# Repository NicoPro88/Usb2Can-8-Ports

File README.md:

# Usb2Can-8-Ports

Carte électronique offrant **8 ports CAN** (jusqu'à **500 kbit/s** chacun) reliés à un PC par **un seul port USB**.

## Objectif

- 8 bus CAN indépendants, isolés ou non (à décider), débit nominal 500 kbit/s (CAN 2.0B, CAN FD envisageable).
- Connexion hôte en USB (USB 2.0 Full Speed ou High Speed, à décider selon la charge).
- Compatibilité visée côté PC : SocketCAN (Linux) et, si possible, un protocole ouvert type gs_usb / candleLight.
- Conception matérielle sous KiCad, firmware embarqué et documentation versionnés dans ce dépôt.

## Organisation du dépôt

| Dossier | Contenu |
|---|---|
| `hardware/` | Projet KiCad (schéma, PCB, bibliothèques, fichiers de fabrication) |
| `firmware/` | Code embarqué du microcontrôleur |
| `docs/` | Cahier des charges, choix d'architecture, notes de conception |

## État

- Architecture décidée : voir [`docs/decisions.md`](docs/decisions.md) (D1 à D6).
- Schéma v0.2 : [`docs/schema-bloc.md`](docs/schema-bloc.md) et [`hardware/`](hardware/).
- Placement des composants des deux cartes (non routé) : [`docs/placement.md`](docs/placement.md).

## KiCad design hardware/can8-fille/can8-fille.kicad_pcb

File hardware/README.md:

# Matériel

Deux cartes empilées (décision D3) :

| Dossier | Carte | Contenu |
|---|---|---|
| `can8-mere/` | Carte mère, 4 couches | STM32H723ZGT6, PHY USB3320 (USB HS), alimentation 9-36 V, ports CAN 1 à 4 |
| `can8-fille/` | Carte fille, 4 couches | ports CAN 5 à 8, reliée par un connecteur 2 × 20 |
| `bibliotheque/` | | symboles absents de la bibliothèque KiCad (USB3320C, ISO1042, UCC12050, MCP2518FD SOIC) |
| `outils/` | | générateur des schémas, vérification de la netlist, placement, routage, sorties de fabrication ; `retouches_mere_v03/` : trace des retouches de la carte mère |
| `fab/v0.3/` | | sorties de la v0.3 : Gerber et perçages, nomenclature, placement CMS, PDF, rendus, pour les deux cartes (le modèle STEP est régénéré par `outils/exporter.sh`, hors git) |

Chaque projet contient le schéma KiCad (`.kicad_pro`, `.kicad_sch`), un export PDF (`*-schema.pdf`), la nomenclature (`*-nomenclature.csv`), le circuit imprimé routé (`.kicad_pcb`, règles complémentaires dans `.kicad_dru`) et la vue PDF du placement v0.2 (`*-placement.pdf`). Les projets s'ouvrent dans **KiCad 9**.
Le schéma-bloc, l'affectation des broches et les points à vérifier sont dans [`docs/schema-bloc.md`](../docs/schema-bloc.md).

## État : v0.3, routage

4 couches, plans de masse et d'alimentation internes pleins. DRC de KiCad 9 sans erreur avec les règles du projet, parité schéma / circuit comprise, sur les deux cartes.

- **Carte fille** : routée à 100 %, sorties de fabrication complètes dans `fab/v0.3/can8-fille/`.
- **Carte mère** : routée à 100 % après une deuxième passe (placement retouché autour du PHY USB, bus ULPI re-tiré, ~INT1 à ~INT3 déplacées sur PG0, PG1, PA11), sorties de fabrication complètes dans `fab/v0.3/can8-mere/`. Avant de commander : relecture dans KiCad et vias dans les pastilles à faire boucher ou à décaler (`docs/routage.md` § 7).

Méthode, résultats, retouches de la carte mère, ce qui est vérifié et ce qui ne l'est pas : [`docs/routage.md`](../docs/routage.md).

```sh
# routage (KiCad 9 + Freerouting 2.5), voir docs/routage.md § 8
python3 hardware/outils/router.py preparer|importer|completer|finir|rapport can8-mere
# sorties de fabrication et rendus dans hardware/fab/v0.3/
sh hardware/outils/exporter.sh v0.3
```

## v0.2 : schémas et placement

Les schémas ont été générés par `outils/generer_schemas.py`, qui décrit chaque carte sous forme de netlist (composant, broche, net) et la dessine en KiCad 7 (lisible par KiCad 8 et 9). `outils/verifier_netlist.py` relit la netlist exportée par `kicad-cli` et la compare à la description : 0 écart sur les deux cartes.

Le dessin est fonctionnel mais brut (étiquettes de nets sur chaque broche). Une fois le schéma validé, on le retouche directement dans KiCad ; le générateur ne doit alors plus être relancé.

Le placement des deux cartes est généré par `outils/placer.py` : gros composants à des positions fixées, passifs placés automatiquement au plus près de leurs broches, contrôles des chevauchements, de la barrière d'isolement, de l'empilage des deux cartes et DRC de KiCad. Détails, images et points à valider : [`docs/placement.md`](../docs/placement.md).

```sh
# régénérer et vérifier (nécessite KiCad 7 : kicad-cli, kicad-symbols, kicad-footprints, module Python pcbnew)
python3 hardware/outils/verifier_netlist.py   # schémas + netlist
python3 hardware/outils/placer.py             # schémas + circuits imprimés placés
```

Les sorties de fabrication (Gerber, BOM, pick & place) sont dans `hardware/fab/<version>/`.

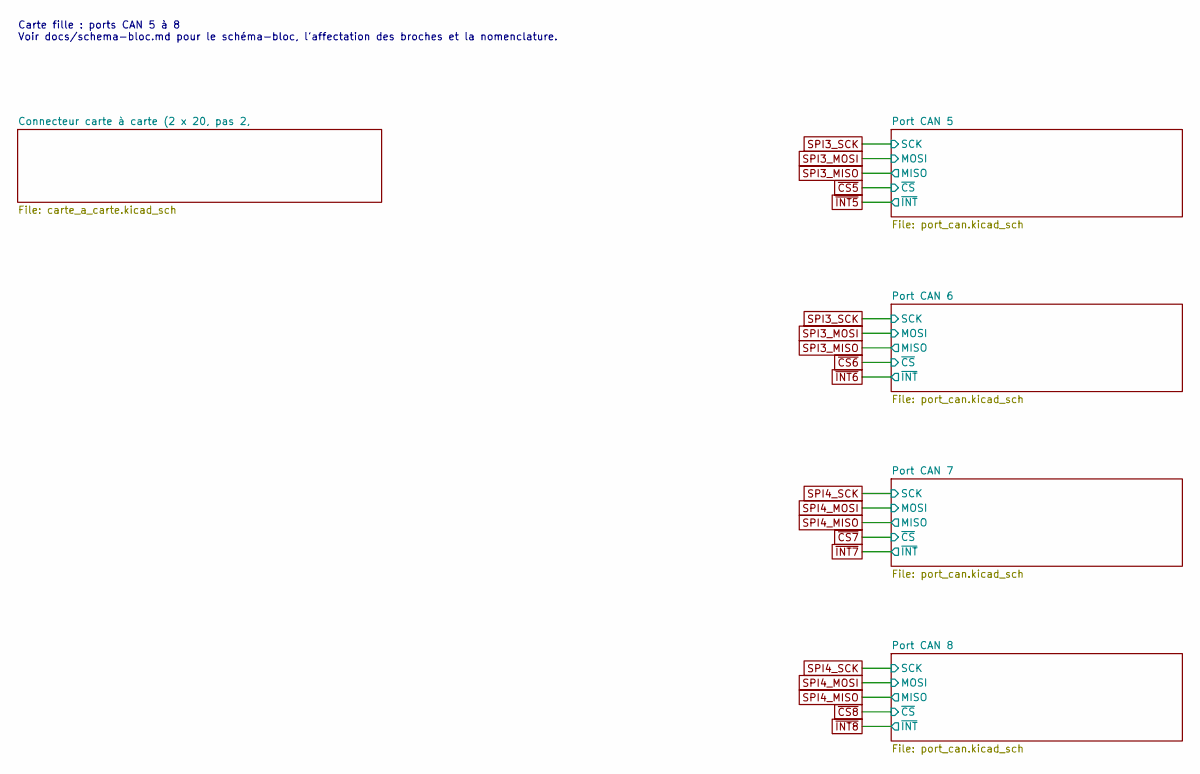
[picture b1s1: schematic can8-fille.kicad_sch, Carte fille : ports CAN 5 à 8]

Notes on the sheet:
Carte fille : ports CAN 5 à 8 Voir docs/schema-bloc.md pour le schéma-bloc, l'affectation des broches et la nomenclature.

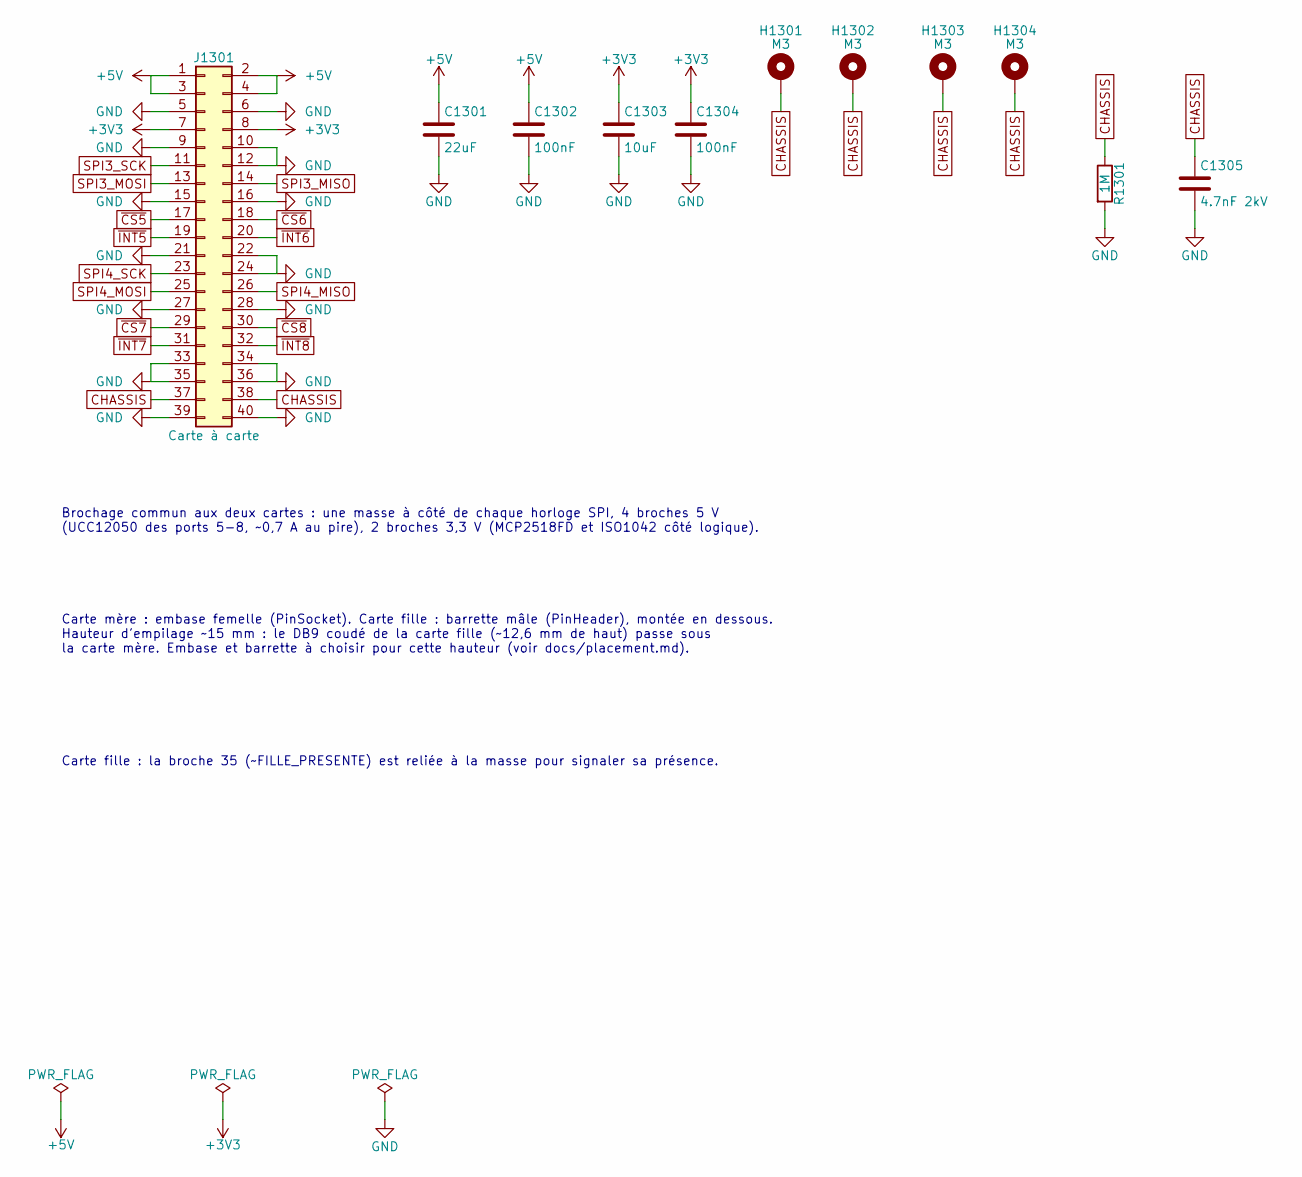
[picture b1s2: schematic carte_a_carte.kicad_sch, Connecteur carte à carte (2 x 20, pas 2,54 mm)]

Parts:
C1301: 22uF; C_1210_3225Metric
C1302, C1304: 100nF; C_0603_1608Metric
C1303: 10uF; C_0805_2012Metric
C1305: 4.7nF 2kV; C_1206_3216Metric
H1301, H1302, H1303, H1304: M3; MountingHole_3.2mm_M3_Pad_Via
J1301: Carte à carte; PinHeader_2x20_P2.54mm_Vertical
R1301: 1M; R_0603_1608Metric

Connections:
+3V3: C1303.1, C1304.1, J1301.7, J1301.8; also elsewhere on the board
+5V: C1301.1, C1302.1, J1301.1, J1301.2, J1301.3, J1301.4; also elsewhere on the board
CHASSIS: C1305.1, H1301.1, H1302.1, H1303.1, H1304.1, J1301.37, J1301.38, R1301.1; also elsewhere on the board
GND: C1301.2, C1302.2, C1303.2, C1304.2, C1305.2, J1301.5, J1301.6, J1301.9, J1301.10, J1301.12, J1301.15, J1301.16, J1301.21, J1301.22, J1301.24, J1301.27, J1301.28, J1301.33, J1301.34, J1301.35, J1301.36, J1301.39, J1301.40, R1301.2; also elsewhere on the board
SPI3_MISO: J1301.14; also elsewhere on the board
SPI3_MOSI: J1301.13; also elsewhere on the board
SPI3_SCK: J1301.11; also elsewhere on the board
SPI4_MISO: J1301.26; also elsewhere on the board
SPI4_MOSI: J1301.25; also elsewhere on the board
SPI4_SCK: J1301.23; also elsewhere on the board
~CS5: J1301.17; also elsewhere on the board
~CS6: J1301.18; also elsewhere on the board
~CS7: J1301.29; also elsewhere on the board
~CS8: J1301.30; also elsewhere on the board
~INT5: J1301.19; also elsewhere on the board
~INT6: J1301.20; also elsewhere on the board
~INT7: J1301.31; also elsewhere on the board
~INT8: J1301.32; also elsewhere on the board

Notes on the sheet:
Brochage commun aux deux cartes : une masse à côté de chaque horloge SPI, 4 broches 5 V (UCC12050 des ports 5-8, ~0,7 A au pire), 2 broches 3,3 V (MCP2518FD et ISO1042 côté logique).
Carte mère : embase femelle (PinSocket). Carte fille : barrette mâle (PinHeader), montée en dessous. Hauteur d'empilage ~15 mm : le DB9 coudé de la carte fille (~12,6 mm de haut) passe sous la carte mère. Embase et barrette à choisir pour cette hauteur (voir docs/placement.md).
Carte fille : la broche 35 (~FILLE_PRESENTE) est reliée à la masse pour signaler sa présence.

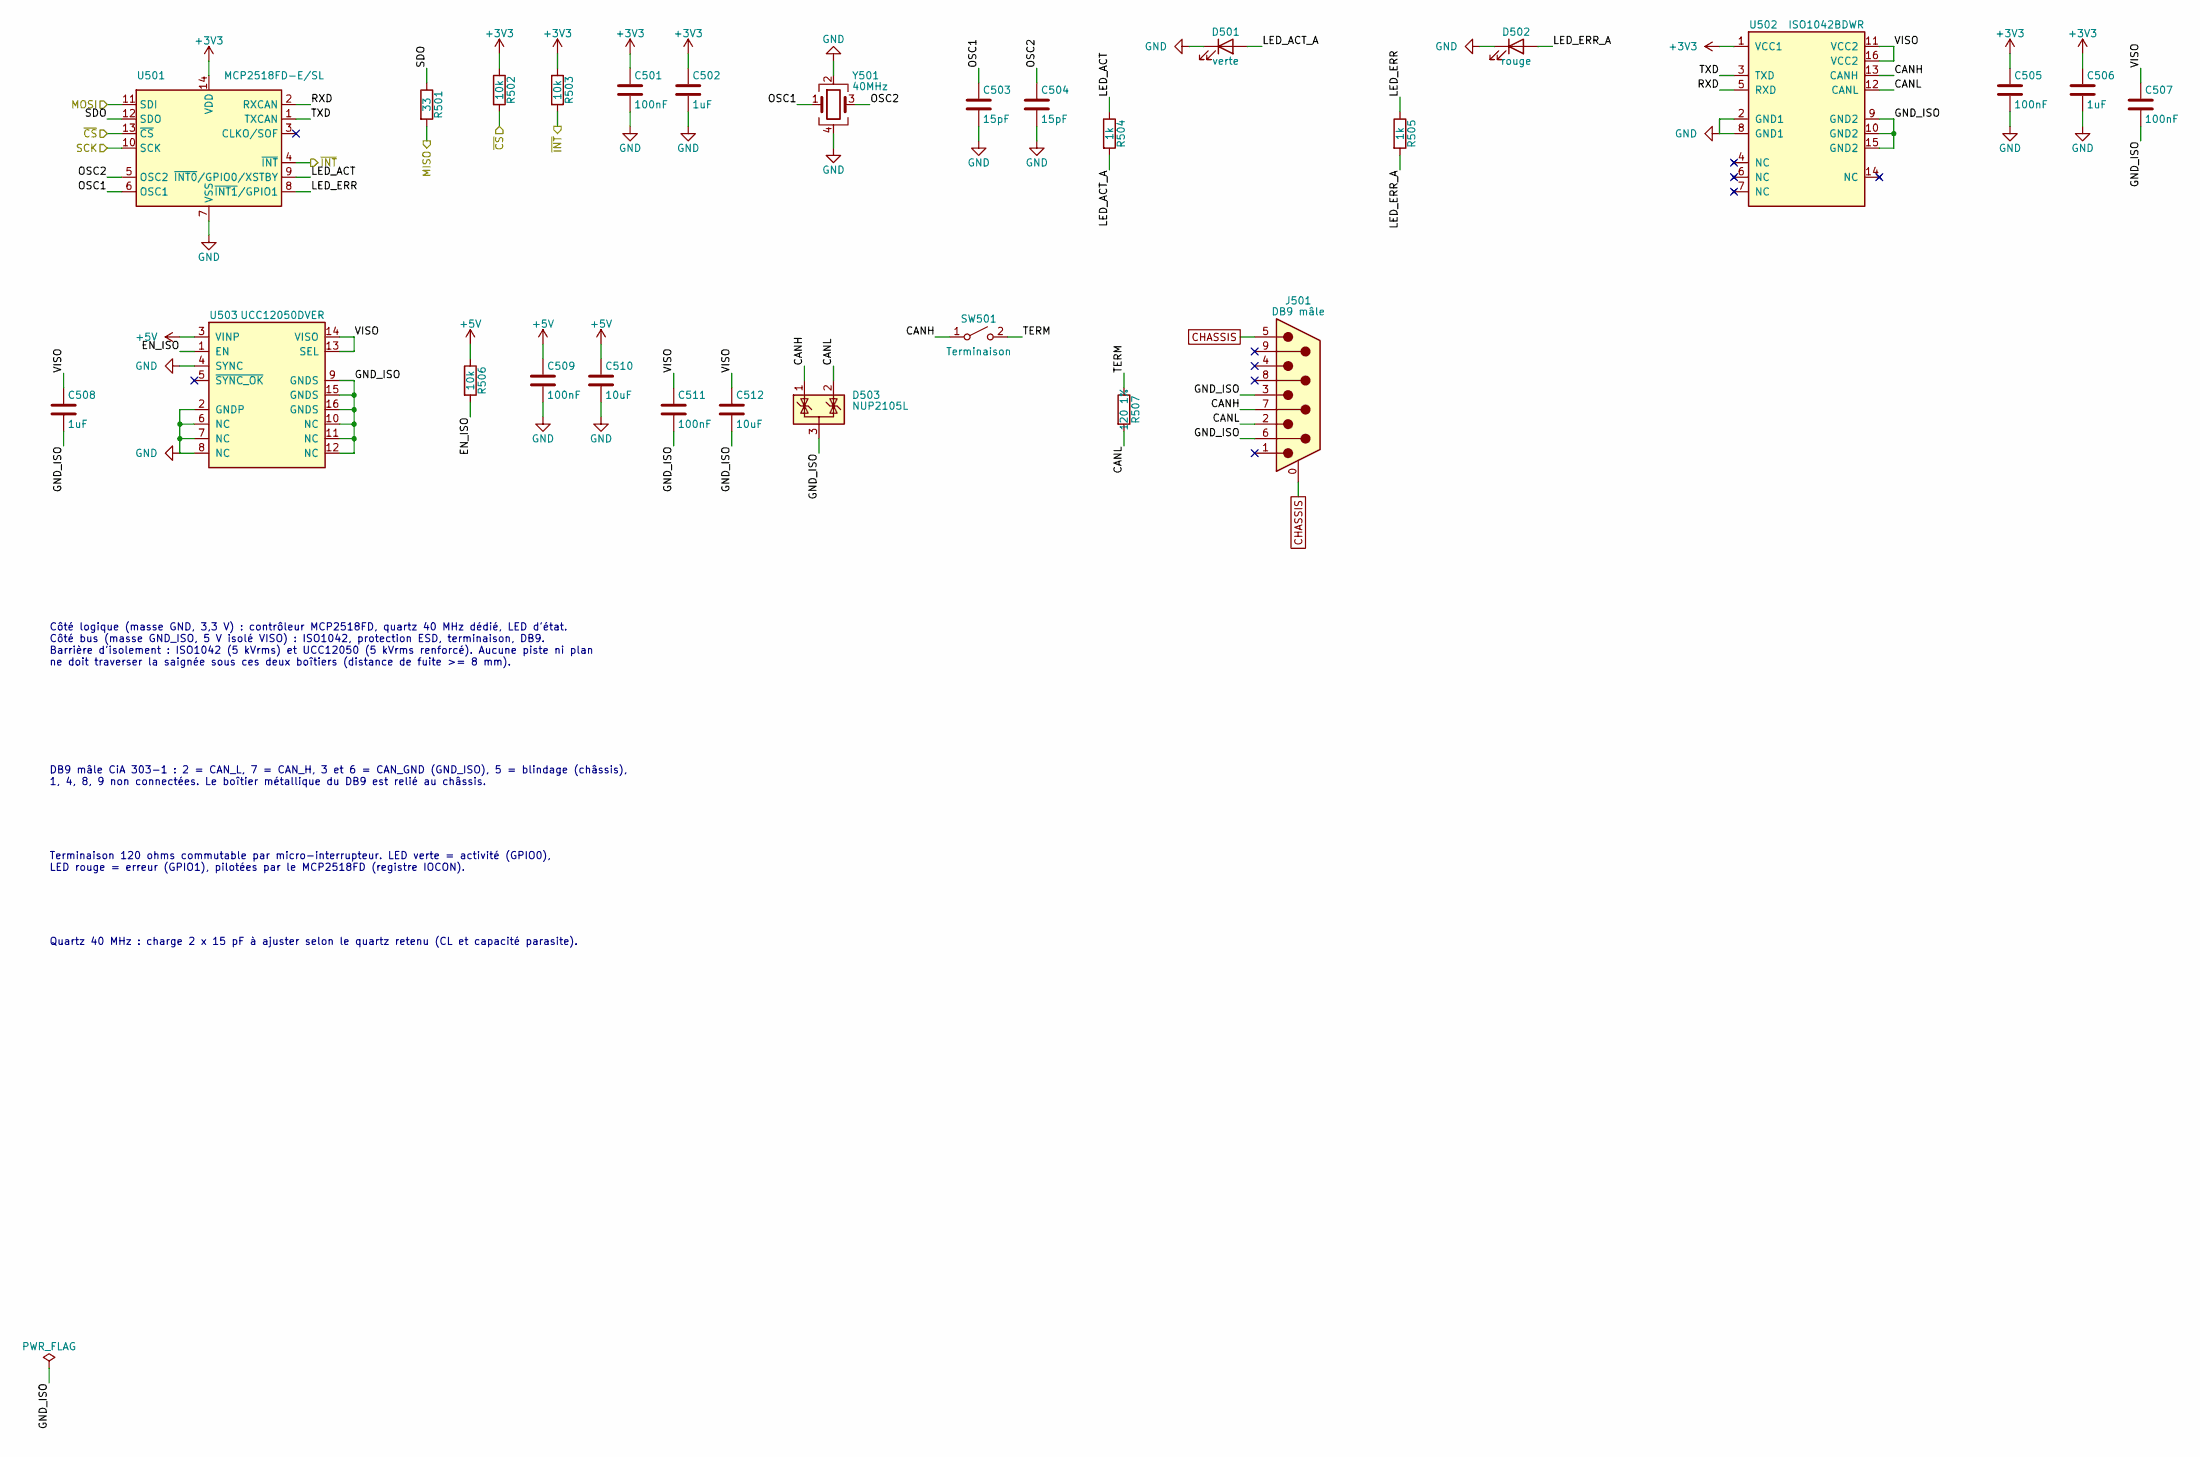
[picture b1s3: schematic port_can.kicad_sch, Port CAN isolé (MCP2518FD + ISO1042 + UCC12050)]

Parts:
C501, C505, C507, C509, C511: 100nF; C_0603_1608Metric
C502, C506, C508: 1uF; C_0805_2012Metric
C503, C504: 15pF; C_0603_1608Metric
C510, C512: 10uF; C_0805_2012Metric
D501: verte; LED_0603_1608Metric
D502: rouge; LED_0603_1608Metric
D503: NUP2105L; SOT-23
J501: DB9 mâle; DSUB-9_Pins_Horizontal_P2.77x2.84mm_EdgePinOffset9.90mm_Hou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
R501: 33; R_0603_1608Metric
R502, R503, R506: 10k; R_0603_1608Metric
R504, R505: 1k; R_0603_1608Metric
R507: 120 1%; R_1206_3216Metric
SW501: Terminaison; SW_DIP_SPSTx01_Slide_6.7x4.1mm_W8.61mm_P2.54mm_LowProfile
U501: MCP2518FD-E/SL; SOIC-14_3.9x8.7mm_P1.27mm
U502: ISO1042BDWR; SOIC-16W_7.5x10.3mm_P1.27mm
U503: UCC12050DVER; SOIC-16W_7.5x10.3mm_P1.27mm
Y501: 40MHz; Crystal_SMD_3225-4Pin_3.2x2.5mm

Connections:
+3V3: C501.1, C502.1, C505.1, C506.1, R502.1, R503.1, U501.14 (VDD), U502.1 (VCC1); also elsewhere on the board
+5V: C509.1, C510.1, R506.1, U503.3 (VINP); also elsewhere on the board
/Port CAN 5/CANH: D503.1 (K), J501.7, SW501.1 (A), U502.13 (CANH)
/Port CAN 5/CANL: D503.2 (K), J501.2, R507.2, U502.12 (CANL)
/Port CAN 5/EN_ISO: R506.2, U503.1 (EN)
/Port CAN 5/GND_ISO: C507.2, C508.2, C511.2, C512.2, D503.3 (A), J501.3, J501.6, U502.9 (GND2), U502.10 (GND2), U502.15 (GND2), U503.9 (GNDS), U503.10 (NC), U503.11 (NC), U503.12 (NC), U503.15 (GNDS), U503.16 (GNDS)
/Port CAN 5/LED_ACT: R504.1, U501.9 (~INT0/GPIO0/XSTBY)
/Port CAN 5/LED_ACT_A: D501.2 (A), R504.2
/Port CAN 5/LED_ERR: R505.1, U501.8 (~INT1/GPIO1)
/Port CAN 5/LED_ERR_A: D502.2 (A), R505.2
/Port CAN 5/OSC1: C503.1, U501.6 (OSC1), Y501.1
/Port CAN 5/OSC2: C504.1, U501.5 (OSC2), Y501.3
/Port CAN 5/RXD: U501.2 (RXCAN), U502.5 (RXD)
/Port CAN 5/SDO: R501.1, U501.12 (SDO)
/Port CAN 5/TERM: R507.1, SW501.2 (B)
/Port CAN 5/TXD: U501.1 (TXCAN), U502.3 (TXD)
/Port CAN 5/VISO: C507.1, C508.1, C511.1, C512.1, U502.11 (VCC2), U502.16 (VCC2), U503.13 (SEL), U503.14 (VISO)
CHASSIS: J501.0 (PAD), J501.5; also elsewhere on the board
GND: C501.2, C502.2, C503.2, C504.2, C505.2, C506.2, C509.2, C510.2, D501.1 (K), D502.1 (K), U501.7 (VSS), U502.2 (GND1), U502.8 (GND1), U503.2 (GNDP), U503.4 (SYNC), U503.6 (NC), U503.7 (NC), U503.8 (NC), Y501.2, Y501.4; also elsewhere on the board
SPI3_MISO: R501.2; also elsewhere on the board
SPI3_MOSI: U501.11 (SDI); also elsewhere on the board
SPI3_SCK: U501.10 (SCK); also elsewhere on the board
~CS5: R502.2, U501.13 (~CS); also elsewhere on the board
~INT5: R503.2, U501.4 (~INT); also elsewhere on the board

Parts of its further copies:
C601, C605, C607, C609, C611, C701, C705, C707, C709, C711, C801, C805, C807, C809, C811: 100nF; C_0603_1608Metric
C602, C606, C608, C702, C706, C708, C802, C806, C808: 1uF; C_0805_2012Metric
C603, C604, C703, C704, C803, C804: 15pF; C_0603_1608Metric
C610, C612, C710, C712, C810, C812: 10uF; C_0805_2012Metric
D601, D701, D801: verte; LED_0603_1608Metric
D602, D702, D802: rouge; LED_0603_1608Metric
D603, D703, D803: NUP2105L; SOT-23
J601, J701, J801: DB9 mâle; DSUB-9_Pins_Horizontal_P2.77x2.84mm_EdgePinOffset9.90mm_Hou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
R601, R701, R801: 33; R_0603_1608Metric
R602, R603, R606, R702, R703, R706, R802, R803, R806: 10k; R_0603_1608Metric
R604, R605, R704, R705, R804, R805: 1k; R_0603_1608Metric
R607, R707, R807: 120 1%; R_1206_3216Metric
SW601, SW701, SW801: Terminaison; SW_DIP_SPSTx01_Slide_6.7x4.1mm_W8.61mm_P2.54mm_LowProfile
U601, U701, U801: MCP2518FD-E/SL; SOIC-14_3.9x8.7mm_P1.27mm
U602, U702, U802: ISO1042BDWR; SOIC-16W_7.5x10.3mm_P1.27mm
U603, U703, U803: UCC12050DVER; SOIC-16W_7.5x10.3mm_P1.27mm
Y601, Y701, Y801: 40MHz; Crystal_SMD_3225-4Pin_3.2x2.5mm

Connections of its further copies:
+3V3: C601.1, C602.1, C605.1, C606.1, C701.1, C702.1, C705.1, C706.1, C801.1, C802.1, C805.1, C806.1, R602.1, R603.1, R702.1, R703.1, R802.1, R803.1, U601.14 (VDD), U602.1 (VCC1), U701.14 (VDD), U702.1 (VCC1), U801.14 (VDD), U802.1 (VCC1); also elsewhere on the board
+5V: C609.1, C610.1, C709.1, C710.1, C809.1, C810.1, R606.1, R706.1, R806.1, U603.3 (VINP), U703.3 (VINP), U803.3 (VINP); also elsewhere on the board
/Port CAN 6/CANH: D603.1 (K), J601.7, SW601.1 (A), U602.13 (CANH)
/Port CAN 6/CANL: D603.2 (K), J601.2, R607.2, U602.12 (CANL)
/Port CAN 6/EN_ISO: R606.2, U603.1 (EN)
/Port CAN 6/GND_ISO: C607.2, C608.2, C611.2, C612.2, D603.3 (A), J601.3, J601.6, U602.9 (GND2), U602.10 (GND2), U602.15 (GND2), U603.9 (GNDS), U603.10 (NC), U603.11 (NC), U603.12 (NC), U603.15 (GNDS), U603.16 (GNDS)
/Port CAN 6/LED_ACT: R604.1, U601.9 (~INT0/GPIO0/XSTBY)
/Port CAN 6/LED_ACT_A: D601.2 (A), R604.2
/Port CAN 6/LED_ERR: R605.1, U601.8 (~INT1/GPIO1)
/Port CAN 6/LED_ERR_A: D602.2 (A), R605.2
/Port CAN 6/OSC1: C603.1, U601.6 (OSC1), Y601.1
/Port CAN 6/OSC2: C604.1, U601.5 (OSC2), Y601.3
/Port CAN 6/RXD: U601.2 (RXCAN), U602.5 (RXD)
/Port CAN 6/SDO: R601.1, U601.12 (SDO)
/Port CAN 6/TERM: R607.1, SW601.2 (B)
/Port CAN 6/TXD: U601.1 (TXCAN), U602.3 (TXD)
/Port CAN 6/VISO: C607.1, C608.1, C611.1, C612.1, U602.11 (VCC2), U602.16 (VCC2), U603.13 (SEL), U603.14 (VISO)
/Port CAN 7/CANH: D703.1 (K), J701.7, SW701.1 (A), U702.13 (CANH)
/Port CAN 7/CANL: D703.2 (K), J701.2, R707.2, U702.12 (CANL)
/Port CAN 7/EN_ISO: R706.2, U703.1 (EN)
/Port CAN 7/GND_ISO: C707.2, C708.2, C711.2, C712.2, D703.3 (A), J701.3, J701.6, U702.9 (GND2), U702.10 (GND2), U702.15 (GND2), U703.9 (GNDS), U703.10 (NC), U703.11 (NC), U703.12 (NC), U703.15 (GNDS), U703.16 (GNDS)
/Port CAN 7/LED_ACT: R704.1, U701.9 (~INT0/GPIO0/XSTBY)
/Port CAN 7/LED_ACT_A: D701.2 (A), R704.2
/Port CAN 7/LED_ERR: R705.1, U701.8 (~INT1/GPIO1)
/Port CAN 7/LED_ERR_A: D702.2 (A), R705.2
/Port CAN 7/OSC1: C703.1, U701.6 (OSC1), Y701.1
/Port CAN 7/OSC2: C704.1, U701.5 (OSC2), Y701.3
/Port CAN 7/RXD: U701.2 (RXCAN), U702.5 (RXD)
/Port CAN 7/SDO: R701.1, U701.12 (SDO)
/Port CAN 7/TERM: R707.1, SW701.2 (B)
/Port CAN 7/TXD: U701.1 (TXCAN), U702.3 (TXD)
/Port CAN 7/VISO: C707.1, C708.1, C711.1, C712.1, U702.11 (VCC2), U702.16 (VCC2), U703.13 (SEL), U703.14 (VISO)
/Port CAN 8/CANH: D803.1 (K), J801.7, SW801.1 (A), U802.13 (CANH)
/Port CAN 8/CANL: D803.2 (K), J801.2, R807.2, U802.12 (CANL)
/Port CAN 8/EN_ISO: R806.2, U803.1 (EN)
/Port CAN 8/GND_ISO: C807.2, C808.2, C811.2, C812.2, D803.3 (A), J801.3, J801.6, U802.9 (GND2), U802.10 (GND2), U802.15 (GND2), U803.9 (GNDS), U803.10 (NC), U803.11 (NC), U803.12 (NC), U803.15 (GNDS), U803.16 (GNDS)
/Port CAN 8/LED_ACT: R804.1, U801.9 (~INT0/GPIO0/XSTBY)
/Port CAN 8/LED_ACT_A: D801.2 (A), R804.2
/Port CAN 8/LED_ERR: R805.1, U801.8 (~INT1/GPIO1)
/Port CAN 8/LED_ERR_A: D802.2 (A), R805.2
/Port CAN 8/OSC1: C803.1, U801.6 (OSC1), Y801.1
/Port CAN 8/OSC2: C804.1, U801.5 (OSC2), Y801.3
/Port CAN 8/RXD: U801.2 (RXCAN), U802.5 (RXD)
/Port CAN 8/SDO: R801.1, U801.12 (SDO)
/Port CAN 8/TERM: R807.1, SW801.2 (B)
/Port CAN 8/TXD: U801.1 (TXCAN), U802.3 (TXD)
/Port CAN 8/VISO: C807.1, C808.1, C811.1, C812.1, U802.11 (VCC2), U802.16 (VCC2), U803.13 (SEL), U803.14 (VISO)
CHASSIS: J601.0 (PAD), J601.5, J701.0 (PAD), J701.5, J801.0 (PAD), J801.5; also elsewhere on the board
GND: C601.2, C602.2, C603.2, C604.2, C605.2, C606.2, C609.2, C610.2, C701.2, C702.2, C703.2, C704.2, C705.2, C706.2, C709.2, C710.2, C801.2, C802.2, C803.2, C804.2, C805.2, C806.2, C809.2, C810.2, D601.1 (K), D602.1 (K), D701.1 (K), D702.1 (K), D801.1 (K), D802.1 (K), U601.7 (VSS), U602.2 (GND1), U602.8 (GND1), U603.2 (GNDP), U603.4 (SYNC), U603.6 (NC), U603.7 (NC), U603.8 (NC), U701.7 (VSS), U702.2 (GND1), U702.8 (GND1), U703.2 (GNDP), U703.4 (SYNC), U703.6 (NC), U703.7 (NC), U703.8 (NC), U801.7 (VSS), U802.2 (GND1), U802.8 (GND1), U803.2 (GNDP), U803.4 (SYNC), U803.6 (NC), U803.7 (NC), U803.8 (NC), Y601.2, Y601.4, Y701.2, Y701.4, Y801.2, Y801.4; also elsewhere on the board
SPI3_MISO: R601.2; also elsewhere on the board
SPI3_MOSI: U601.11 (SDI); also elsewhere on the board
SPI3_SCK: U601.10 (SCK); also elsewhere on the board
SPI4_MISO: R701.2, R801.2; also elsewhere on the board
SPI4_MOSI: U701.11 (SDI), U801.11 (SDI); also elsewhere on the board
SPI4_SCK: U701.10 (SCK), U801.10 (SCK); also elsewhere on the board
~CS6: R602.2, U601.13 (~CS); also elsewhere on the board
~CS7: R702.2, U701.13 (~CS); also elsewhere on the board
~CS8: R802.2, U801.13 (~CS); also elsewhere on the board
~INT6: R603.2, U601.4 (~INT); also elsewhere on the board
~INT7: R703.2, U701.4 (~INT); also elsewhere on the board
~INT8: R803.2, U801.4 (~INT); also elsewhere on the board

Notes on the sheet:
Côté logique (masse GND, 3,3 V) : contrôleur MCP2518FD, quartz 40 MHz dédié, LED d'état. Côté bus (masse GND_ISO, 5 V isolé VISO) : ISO1042, protection ESD, terminaison, DB9. Barrière d'isolement : ISO1042 (5 kVrms) et UCC12050 (5 kVrms renforcé). Aucune piste ni plan ne doit traverser la saignée s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
DB9 mâle CiA 303-1 : 2 = CAN_L, 7 = CAN_H, 3 et 6 = CAN_GND (GND_ISO), 5 = blindage (châssis), 1, 4, 8, 9 non connectées. Le boîtier métallique du DB9 est relié au châssis.
Terminaison 120 ohms commutable par micro-interrupteur. LED verte = activité (GPIO0), LED rouge = erreur (GPIO1), pilotées par le MCP2518FD (registre IOCON).
Quartz 40 MHz : charge 2 x 15 pF à ajuster selon le quartz retenu (CL et capacité parasite).

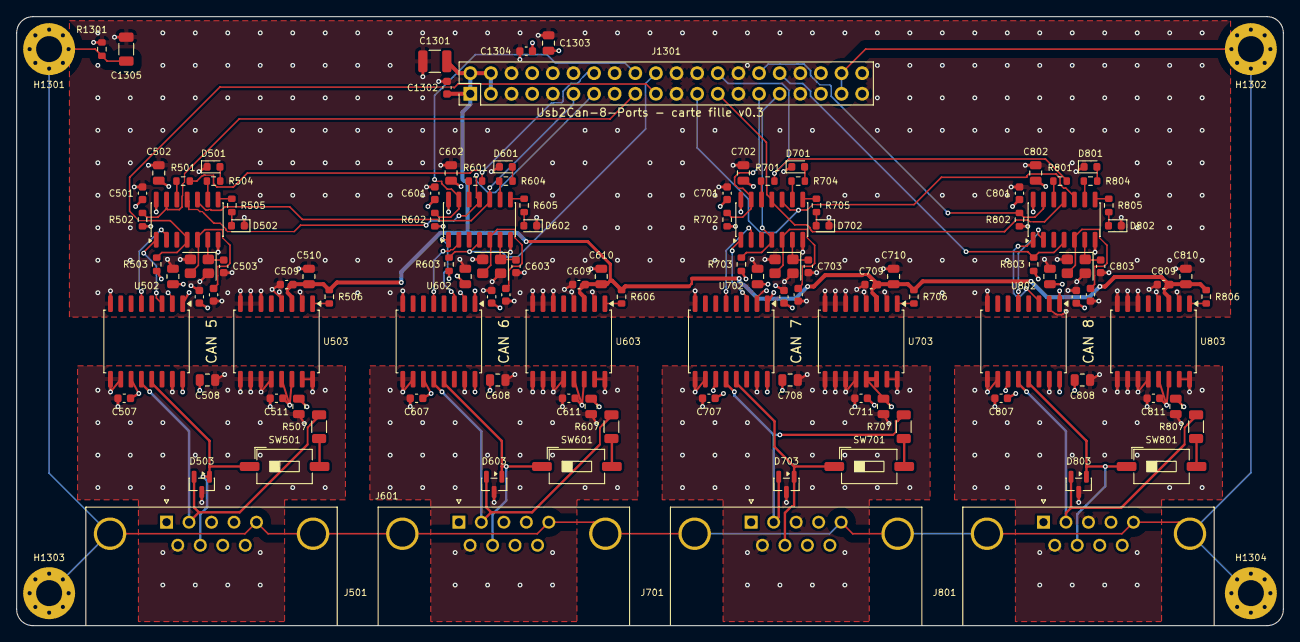
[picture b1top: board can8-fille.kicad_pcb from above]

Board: 4 copper layers, 156.0 x 75.0 mm, 123 parts (0 on the bottom side), 78 nets.

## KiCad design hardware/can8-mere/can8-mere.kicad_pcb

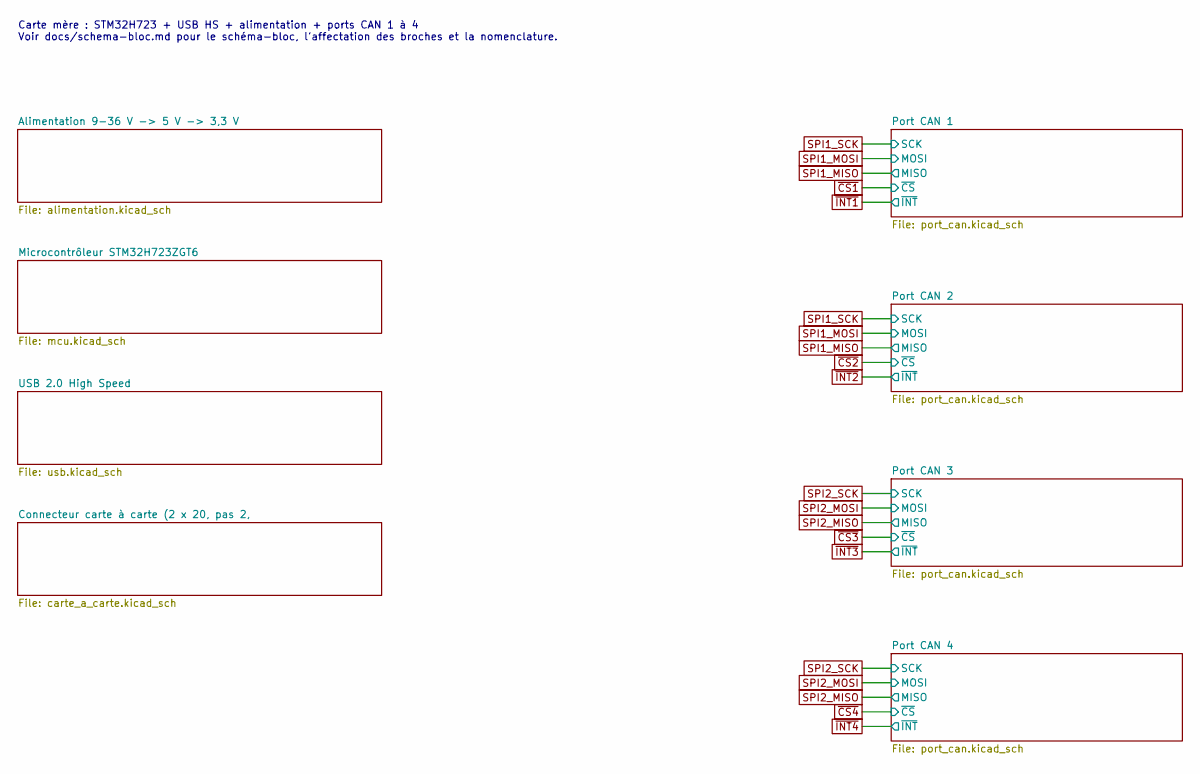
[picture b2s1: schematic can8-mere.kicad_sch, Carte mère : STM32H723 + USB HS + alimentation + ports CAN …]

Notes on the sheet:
Carte mère : STM32H723 + USB HS + alimentation + ports CAN 1 à 4 Voir docs/schema-bloc.md pour le schéma-bloc, l'affectation des broches et la nomenclature.

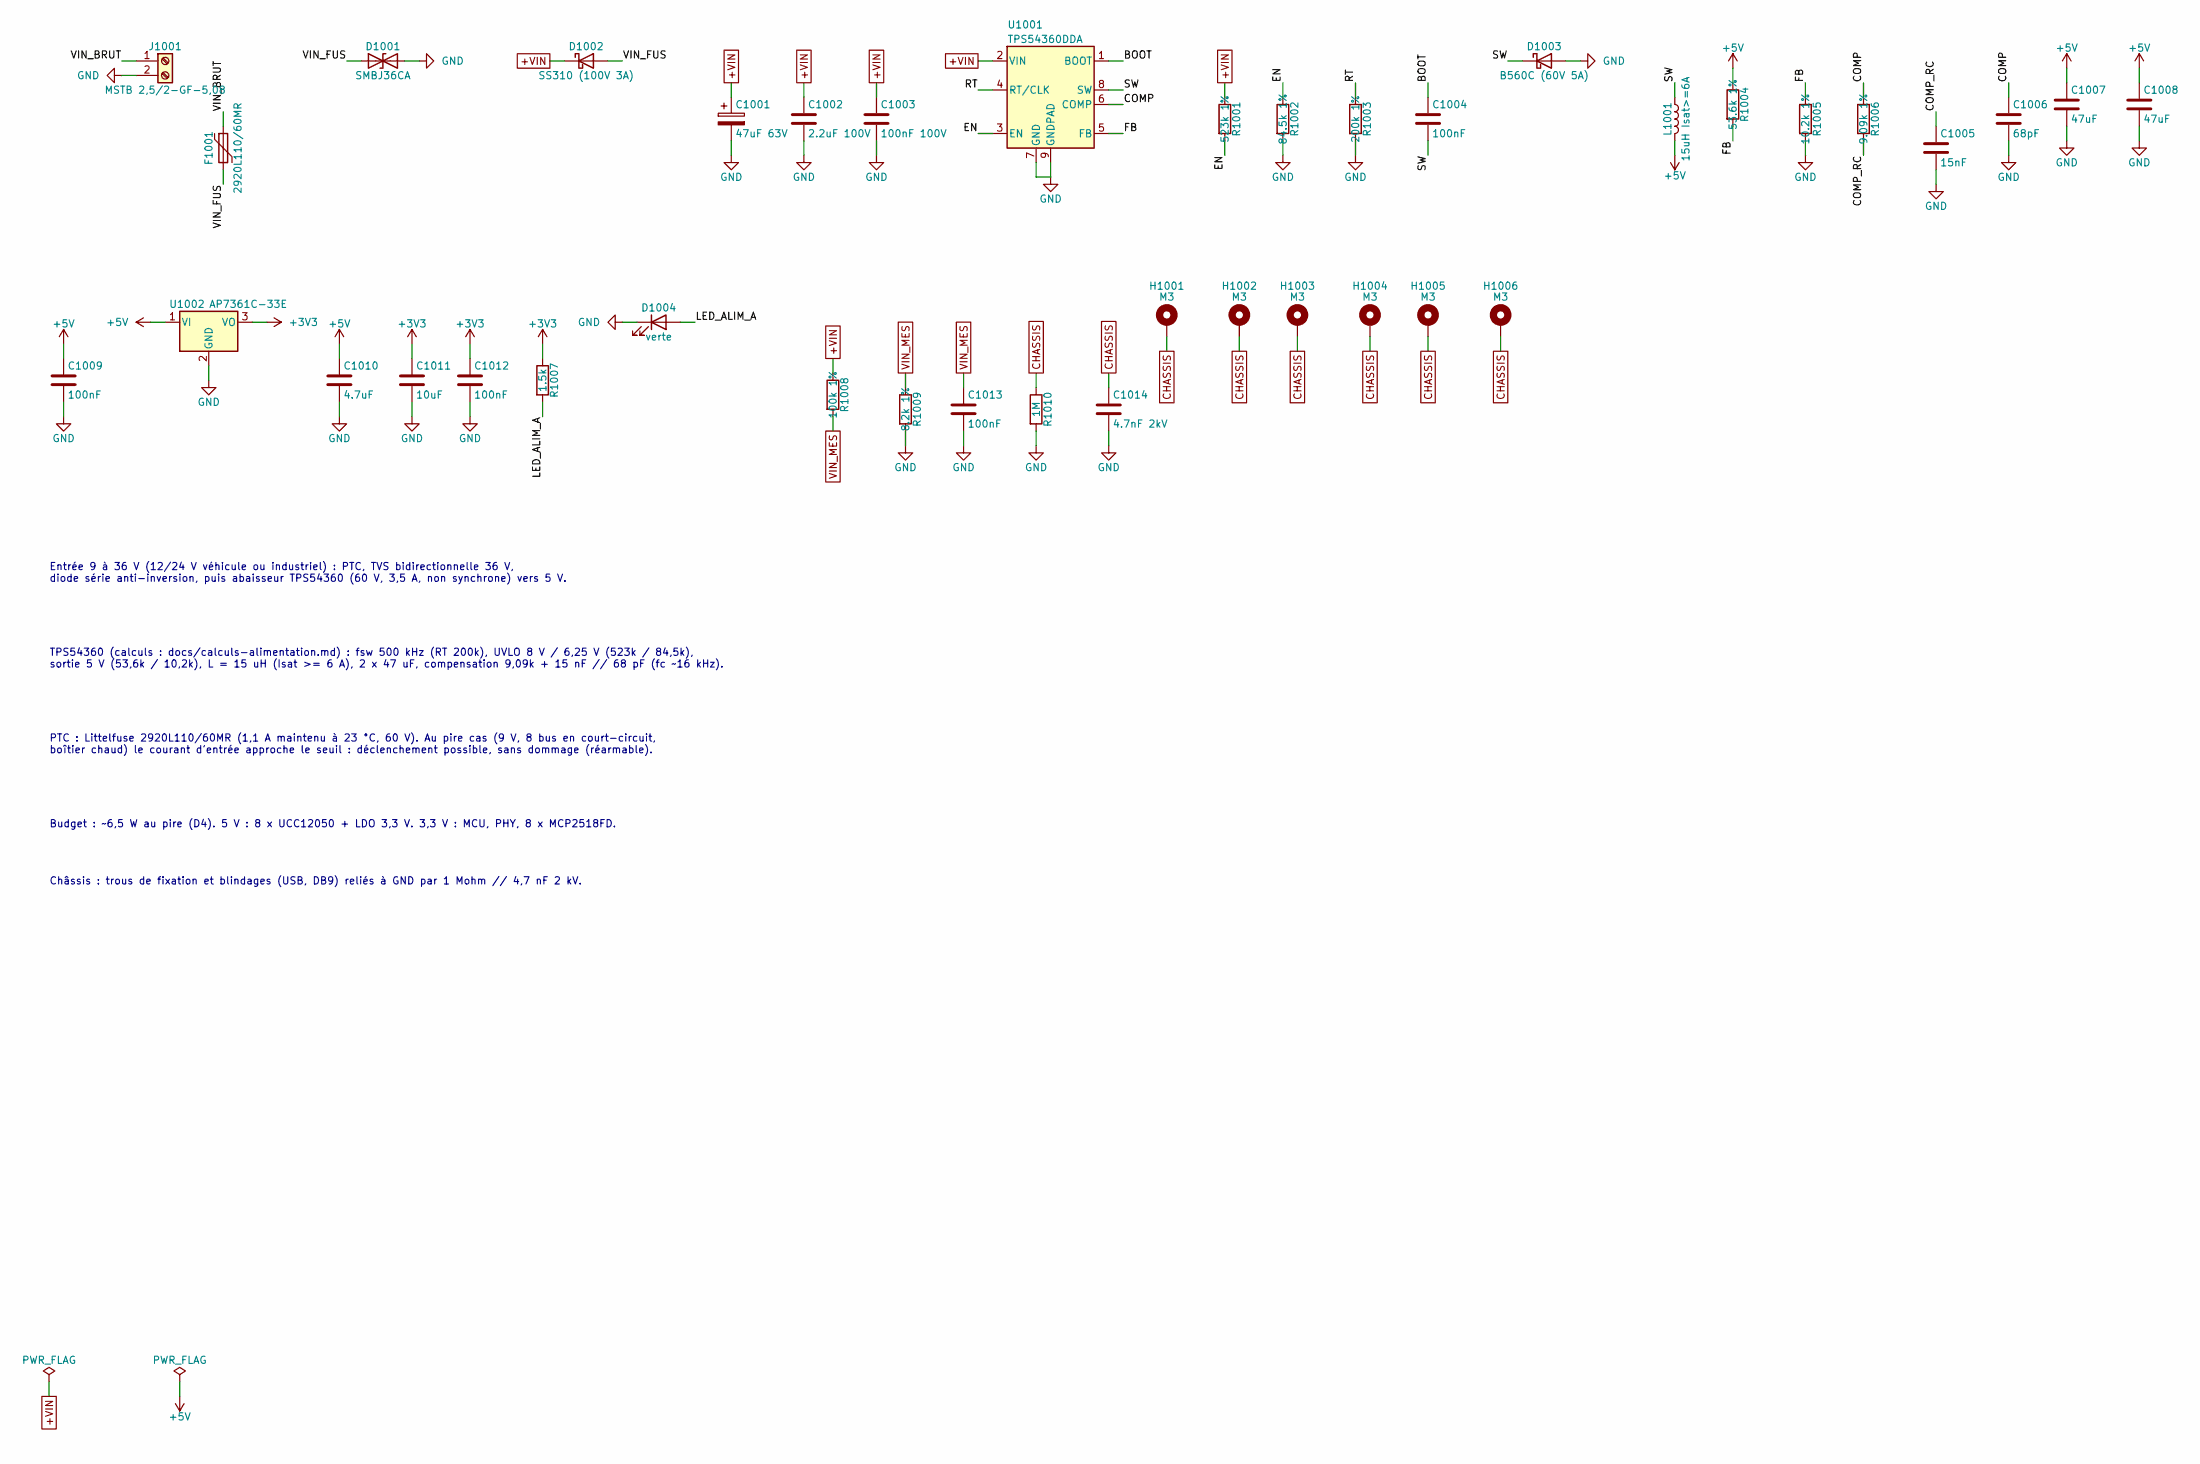
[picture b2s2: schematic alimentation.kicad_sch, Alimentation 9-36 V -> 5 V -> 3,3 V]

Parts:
C1001: 47uF 63V; CP_Elec_8x10
C1002: 2.2uF 100V; C_1210_3225Metric
C1003: 100nF 100V; C_0805_2012Metric
C1004, C1009, C1012, C1013: 100nF; C_0603_1608Metric
C1005: 15nF; C_0603_1608Metric
C1006: 68pF; C_0603_1608Metric
C1007, C1008: 47uF; C_1210_3225Metric
C1010: 4.7uF; C_0805_2012Metric
C1011: 10uF; C_0805_2012Metric
C1014: 4.7nF 2kV; C_1206_3216Metric
D1001: SMBJ36CA; D_SMB
D1002: SS310 (100V 3A); D_SMA
D1003: B560C (60V 5A); D_SMC
D1004: verte; LED_0603_1608Metric
F1001: 2920L110/60MR; Fuse_2920_7451Metric
H1001, H1002, H1003, H1004, H1005, H1006: M3; MountingHole_3.2mm_M3_Pad_Via
J1001: MSTB 2,5/2-GF-5,08; PhoenixContact_MSTB_2,5_2-GF-5,08_1x02_P5.08mm_Horizontal_T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
L1001: 15uH Isat>=6A; L_Bourns_SRP1038C_10.0x10.0mm
R1001: 523k 1%; R_0603_1608Metric
R1002: 84.5k 1%; R_0603_1608Metric
R1003: 200k 1%; R_0603_1608Metric
R1004: 53.6k 1%; R_0603_1608Metric
R1005: 10.2k 1%; R_0603_1608Metric
R1006: 9.09k 1%; R_0603_1608Metric
R1007: 1.5k; R_0603_1608Metric
R1008: 100k 1%; R_0603_1608Metric
R1009: 8.2k 1%; R_0603_1608Metric
R1010: 1M; R_0603_1608Metric
U1001: TPS54360DDA; TI_SO-PowerPAD-8_ThermalVias
U1002: AP7361C-33E; SOT-223-3_TabPin2

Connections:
+3V3: C1011.1, C1012.1, R1007.1, U1002.3 (VO); also elsewhere on the board
+5V: C1007.1, C1008.1, C1009.1, C1010.1, L1001.2, R1004.1, U1002.1 (VI); also elsewhere on the board
+VIN: C1001.1, C1002.1, C1003.1, D1002.1 (K), R1001.1, R1008.1, U1001.2 (VIN)
/Alimentation 9-36 V -> 5 V -> 3,3 V/BOOT: C1004.1, U1001.1 (BOOT)
/Alimentation 9-36 V -> 5 V -> 3,3 V/COMP: C1006.1, R1006.1, U1001.6 (COMP)
/Alimentation 9-36 V -> 5 V -> 3,3 V/COMP_RC: C1005.1, R1006.2
/Alimentation 9-36 V -> 5 V -> 3,3 V/EN: R1001.2, R1002.1, U1001.3 (EN)
/Alimentation 9-36 V -> 5 V -> 3,3 V/FB: R1004.2, R1005.1, U1001.5 (FB)
/Alimentation 9-36 V -> 5 V -> 3,3 V/LED_ALIM_A: D1004.2 (A), R1007.2
/Alimentation 9-36 V -> 5 V -> 3,3 V/RT: R1003.1, U1001.4 (RT/CLK)
/Alimentation 9-36 V -> 5 V -> 3,3 V/SW: C1004.2, D1003.1 (K), L1001.1, U1001.8 (SW)
/Alimentation 9-36 V -> 5 V -> 3,3 V/VIN_BRUT: F1001.1, J1001.1
/Alimentation 9-36 V -> 5 V -> 3,3 V/VIN_FUS: D1001.1 (A1), D1002.2 (A), F1001.2
CHASSIS: C1014.1, H1001.1, H1002.1, H1003.1, H1004.1, H1005.1, H1006.1, R1010.1; also elsewhere on the board
GND: C1001.2, C1002.2, C1003.2, C1005.2, C1006.2, C1007.2, C1008.2, C1009.2, C1010.2, C1011.2, C1012.2, C1013.2, C1014.2, D1001.2 (A2), D1003.2 (A), D1004.1 (K), J1001.2, R1002.2, R1003.2, R1005.2, R1009.2, R1010.2, U1001.7 (GND), U1001.9 (GNDPAD), U1002.2 (GND); also elsewhere on the board
VIN_MES: C1013.1, R1008.2, R1009.1; also elsewhere on the board

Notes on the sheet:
Entrée 9 à 36 V (12/24 V véhicule ou industriel) : PTC, TVS bidirectionnelle 36 V, diode série anti-inversion, puis abaisseur TPS54360 (60 V, 3,5 A, non synchrone) vers 5 V.
TPS54360 (calculs : docs/calculs-alimentation.md) : fsw 500 kHz (RT 200k), UVLO 8 V / 6,25 V (523k / 84,5k), sortie 5 V (53,6k / 10,2k), L = 15 uH (Isat >= 6 A), 2 x 47 uF, compensation 9,09k + 15 nF // 68 pF (fc ~16 kHz).
PTC : Littelfuse 2920L110/60MR (1,1 A maintenu à 23 °C, 60 V). Au pire cas (9 V, 8 bus en court-circuit, boîtier chaud) le courant d'entrée approche le seuil : déclenchement possible, sans dommage (réarmable).
Budget : ~6,5 W au pire (D4). 5 V : 8 x UCC12050 + LDO 3,3 V. 3,3 V : MCU, PHY, 8 x MCP2518FD.
Châssis : trous de fixation et blindages (USB, DB9) reliés à GND par 1 Mohm // 4,7 nF 2 kV.
